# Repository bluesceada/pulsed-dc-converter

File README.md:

# pulsed-dc-converter
12-20V DC to Pulsed DC Converter

Transforms 12-20V DC to a kind of pulsed DC, compatible with some Power Tools using phase cutting
control (for example Proxxon Micromot), in the range up to around 40W.

Like that, with the respective Adapter, those small Power Tools can be operated from a USB C PD
Power Bank. Adapter Example: https://aliexpress.com/wholesale?SearchText=power+adapter+usb+c+dc+20v

**Progress:**

 [x] Simple loop works on breadboard with similar schematic as in kicad
 
 [x] PCB designed and ordered
 
 [x] PCB tested and working with 12V/1.5A from USB-C Powerbank and 20V/3A from USB-C Power Supply (with respective USB-C Adapters). Populated parts are mainly as in the schematic, except the Zener(D3) in the flyback path is just bridged with a wire, see [21861574f8b53dd02fe86965473d7c7fb414512f](https://github.com/bluesceada/pulsed-dc-converter/commit/21861574f8b53dd02fe86965473d7c7fb414512f)
 
 [x] Use ADC feedback to increase the ON-time of the transistor to maximize power for powerbanks

**Note:** I still have PCBs ([Rev-0.1](https://github.com/bluesceada/pulsed-dc-converter/releases/tag/Rev-0.1)) available, message me if you are interested to get it for net cost, ~1€ + shipping from DE/Germany 🇩🇪. I also still have 2x attiny85 that I could pre-program if needed. The only real PCB-errata is a missing connection of Attiny Pin 5 (PB0) to R1, which is easily bridged.

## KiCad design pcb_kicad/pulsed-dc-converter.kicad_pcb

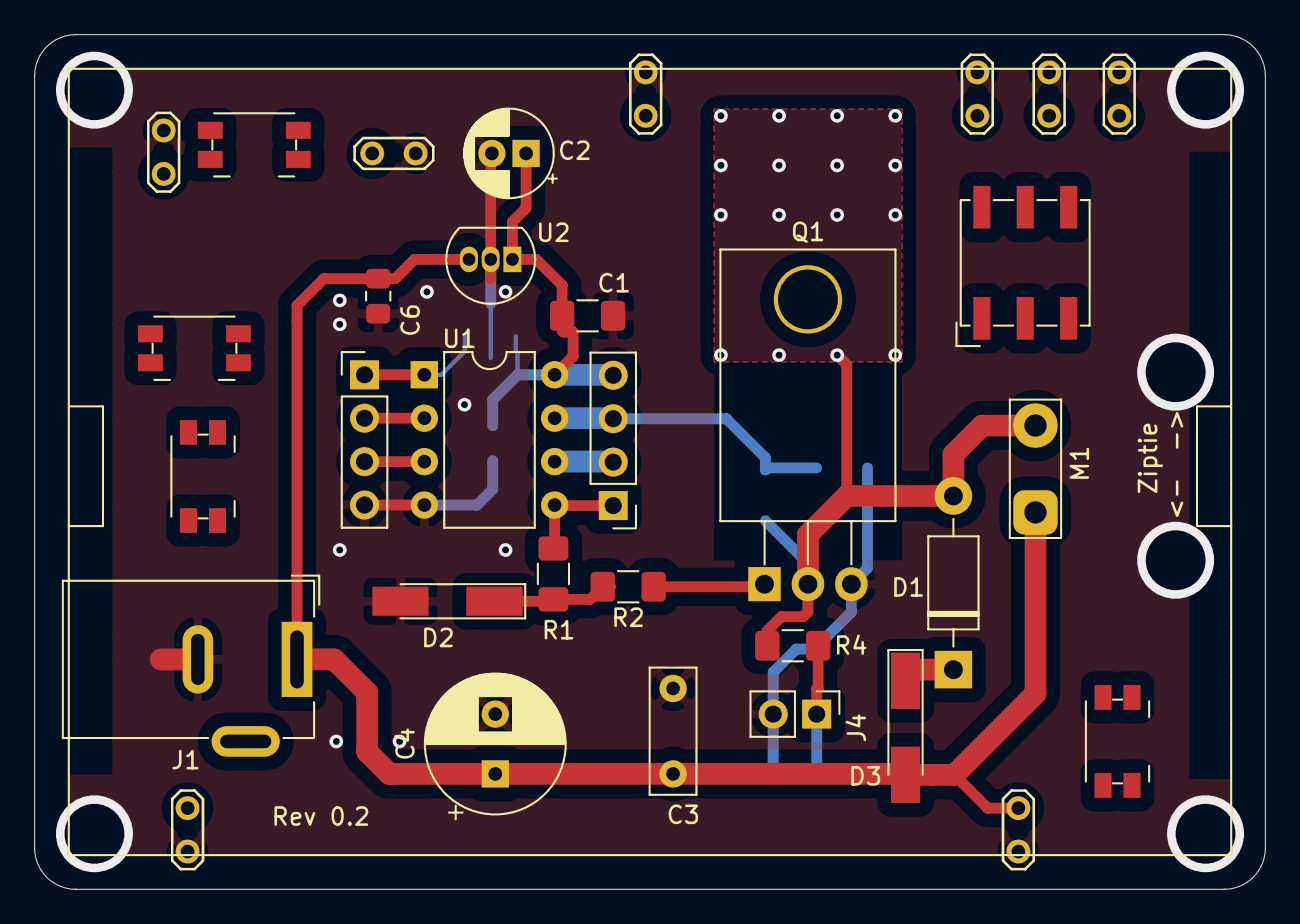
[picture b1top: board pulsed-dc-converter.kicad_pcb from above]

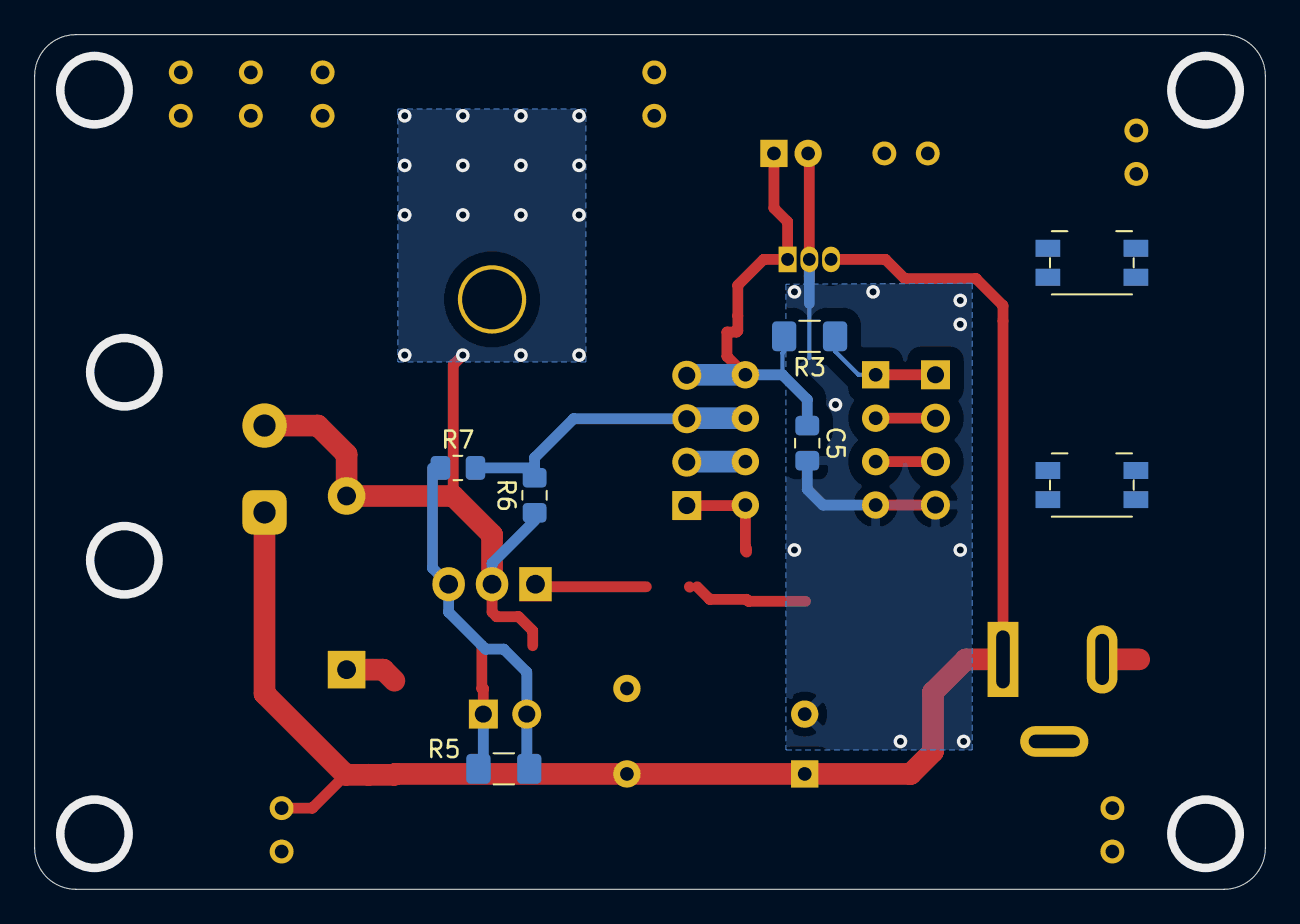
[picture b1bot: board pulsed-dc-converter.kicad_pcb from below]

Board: 2 copper layers, 72.0 x 50.0 mm, 31 parts (7 on the bottom side), 14 nets.

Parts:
C1: 100n; C_1206_3216Metric_Pad1.42x1.75mm_HandSolder
C2: 10u; CP_Radial_D5.0mm_P2.00mm
C3: 100n Foil; C_Rect_L7.2mm_W2.5mm_P5.00mm_FKS2_FKP2_MKS2_MKP2
C4: 470u; CP_Radial_D8.0mm_P3.50mm
C5, C6: 10n; C_0805_2012Metric_Pad1.15x1.40mm_HandSolder
D1: 1N4004; D_DO-41_SOD81_P10.16mm_Horizontal
D2: 5.6V; D_MiniMELF_Handsoldering
D3: 5.6V or Wire; D_MiniMELF_Handsoldering
J1: Conn_01x02_Female; BarrelJack_Wuerth_6941xx301002
J2: AttinyPins2; PinHeader_1x04_P2.54mm_Vertical
J3: AttinyPins1; PinHeader_1x04_P2.54mm_Vertical
J4: Conn_01x02_Female; PinHeader_1x02_P2.54mm_Vertical
M1: Motor_DC; TestPoint_2Pads_Pitch5.08mm_Drill1.3mm
Q1: IRLZ34N or RFP14N05; TO-220-3_Horizontal_TabDown
R1: 10R; R_1206_3216Metric_Pad1.42x1.75mm_HandSolder
R2: 33R; R_1206_3216Metric_Pad1.42x1.75mm_HandSolder
R3: 22k; R_1206_3216Metric_Pad1.42x1.75mm_HandSolder
R4, R5: 10k; R_1206_3216Metric_Pad1.42x1.75mm_HandSolder
R6: 100k; R_0805_2012Metric_Pad1.15x1.40mm_HandSolder
R7: 10k; R_0805_2012Metric_Pad1.15x1.40mm_HandSolder
Reserved: Panasonic_EVQPUK_EVQPUB
Reserved#2, Reserved#3, Reserved#4, Reserved#5, Reserved#6: Panasonic_EVQPUK_EVQPUB
Reserved#7: Nidec_Copal_SH-7010A
U1: ATtiny25-20PU; DIP-8_W7.62mm
U2: LP2950-5.0; TO-92_Inline

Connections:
0: C1.2, C2.2, C3.2, C4.2, C5.2, C6.2, D2.2, J1.2, J3.4, J4.2, Q1.3, R5.1, R7.1, U1.4, U2.2
+12V: C3.1, C4.1, C6.1, D3.2, J1.1, M1.1, U2.3
unnamed: C1.1, C2.1, C5.1, J2.4, R3.2, U1.8, U2.1
unnamed: D1.1, D3.1
unnamed: D1.2, M1.2, Q1.2, R4.2, R6.1
unnamed: D2.1, R1.1, R2.2
unnamed: J2.1, R1.2, U1.5
unnamed: J2.2, U1.6
unnamed: J2.3, R6.2, R7.2, U1.7
unnamed: J3.1, R3.1, U1.1
unnamed: J3.2, U1.2
unnamed: J3.3, U1.3
unnamed: J4.1, R4.1, R5.2
unnamed: Q1.1, R2.1

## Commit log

2021-11-29 updated project description
2021-11-30 upd readme
2021-11-30 basic project that runs on the attiny to control the transistor
2021-11-30 experimental setup of the breadboard
2021-11-30 sigrok measurements that were done on the breadboard circuit example
2021-11-30 Kicad-designed PCB, including minor Spice Simulation (but seems not very realistic...)
    PCB size 72mm x 50mm with screws in the corners for a specific box size I have here
    Most major change to breadboard measurements:
    - Added Zener in Flyback Path - not sure if this will be really used, but it will be an option on the PCB.
    - Slightly different choices in some capacitors and resistors.
    - No LED
2021-11-30 screenshot of pcb in kicad to get a first impression
2021-12-06 keepout below transistor (metal/drain is there)
2022-01-19 Final TESTED, working PCB - Tested with following population alternatives and current git attiny code:
    C4: 360u + 100u on TP0 reserve slot (no fitting form factor 470u Capacitor with >20V tolerance was available)
    D3: Wire
    R2: 22 (33 was not available, but should work either way)
    R6: 100k
    R7: 10.5k
    R4: 22.1k
2022-01-19 (not important: use other programmer again)
2022-01-19 Code designated to consume more power from powerbanks using ADC-feedback (not actually measured if it does use more power, but the transistor ON-time is longer)
2022-01-19 Various PCB adjustments for a better Rev 02
2022-01-19 measurements from PCB (can be opened with sigrok/pulseview)
    for 12V powerbank and 19V from USB-C PD supply, with current git code (ADC-feedback used)
2022-01-19 working pcb setup picture and updated kicad screenshot
2022-01-19 schematic screenshot png
2022-01-27 more rounded PCB corners
